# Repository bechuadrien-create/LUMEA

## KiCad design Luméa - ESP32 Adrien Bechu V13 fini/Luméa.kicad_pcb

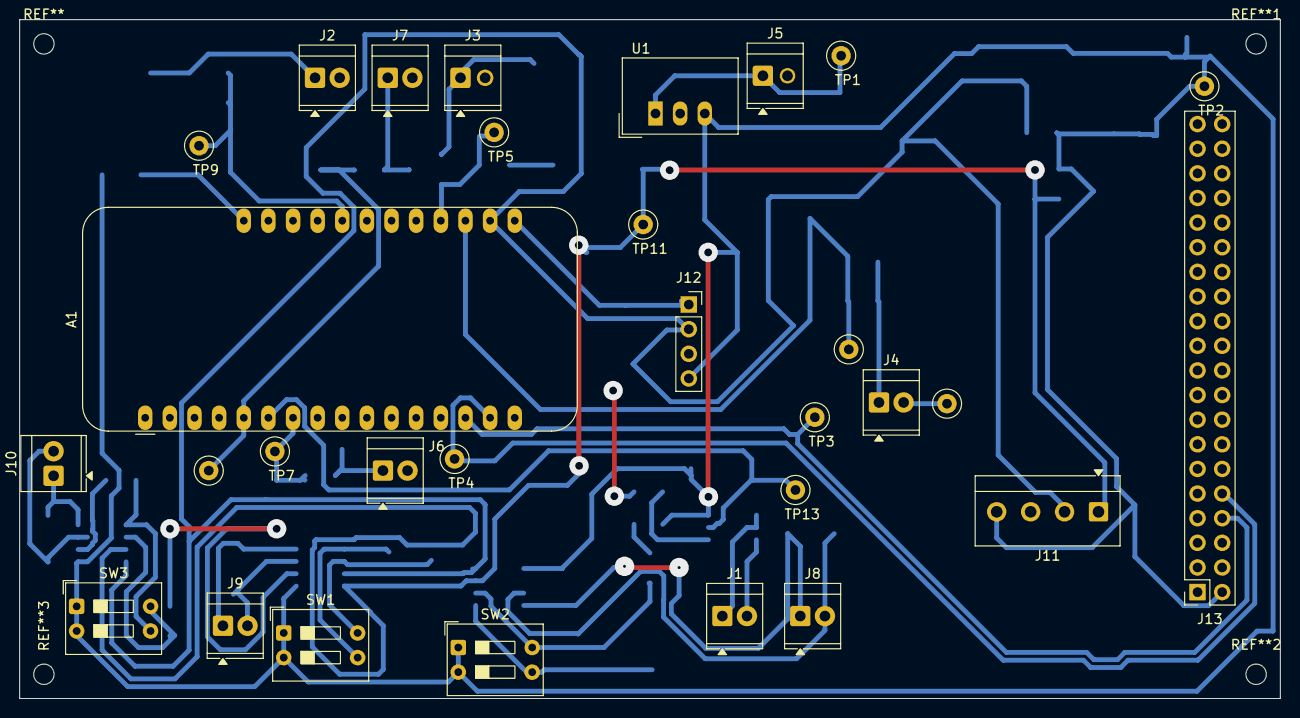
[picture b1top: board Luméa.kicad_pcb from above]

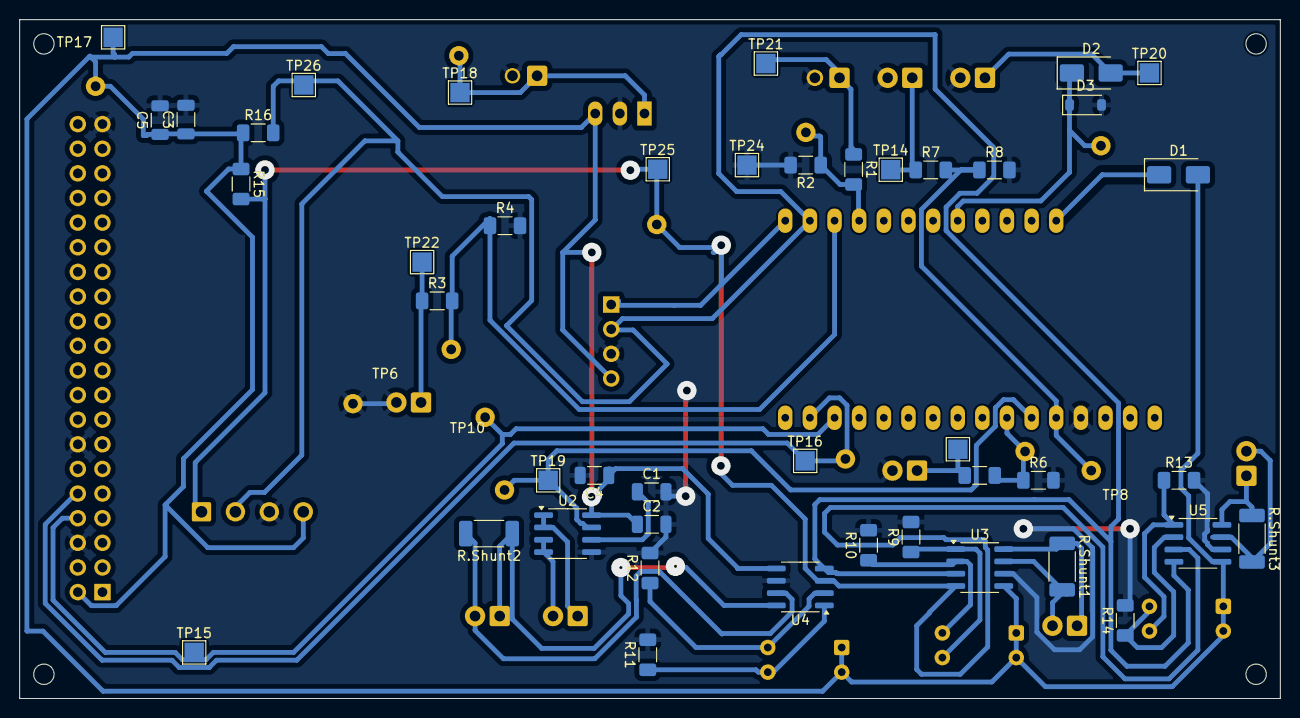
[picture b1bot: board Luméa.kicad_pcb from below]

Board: 2 copper layers, 130.0 x 70.0 mm, 74 parts (44 on the bottom side), 34 nets.

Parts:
A1: Adafruit_Feather_HUZZAH32_ESP32; Adafruit_Feather
C1: 100nF; C_1206_3216Metric
C2: 1nF; C_1206_3216Metric
C3, C4, C5: 1μF; C_1206_3216Metric
D1: B120-E3; D_SMA
D2: D; D_SMA
D3: D_Zener; D_SOD-123
J1, J3, J4, J5, J6, J7, J8, J9, J10: Screw_Terminal_01x02; TerminalBlock_TE_282834-2_1x02_P2.54mm_Horizontal
J2: Tension des panneaux photovoltaiques; TerminalBlock_TE_282834-2_1x02_P2.54mm_Horizontal
J11: BMP 280; TerminalBlock_4Ucon_1x04_P3.50mm_Horizontal
J12: TF051; PinSocket_1x04_P2.54mm_Vertical
J13: GPIO; PinSocket_2x20_P2.54mm_Vertical
R1, R3, R5, R7: 22K; R_1206_3216Metric_Pad1.30x1.75mm_HandSolder
R2, R4, R6, R8, R9, R10, R11, R12, R13, R14: 10K; R_1206_3216Metric_Pad1.30x1.75mm_HandSolder
R15: 4.7K; R_1206_3216Metric_Pad1.30x1.75mm_HandSolder
R16: 4.7k; R_1206_3216Metric_Pad1.30x1.75mm_HandSolder
R.Shunt1, R.Shunt2, R.Shunt3: 0.1; R_2010_5025Metric_Pad1.40x2.65mm_HandSolder
SW1, SW2, SW3: SW_DIP_x02; SW_DIP_SPSTx02_Slide_9.78x7.26mm_W7.62mm_P2.54mm
TP1: Test 12V; TestPoint_Loop_D2.50mm_Drill1.0mm_LowProfile
TP2: Test 5V; TestPoint_Loop_D2.50mm_Drill1.0mm_LowProfile
TP3: Test RX; TestPoint_Loop_D2.50mm_Drill1.0mm_LowProfile
TP4: Test TX; TestPoint_Loop_D2.50mm_Drill1.0mm_LowProfile
TP5, TP6, TP7, TP9, TP13: TestPoint; TestPoint_Loop_D2.50mm_Drill1.0mm_LowProfile
TP8: Batterie; TestPoint_Loop_D2.50mm_Drill1.0mm_LowProfile
TP10: Test GND; TestPoint_Loop_D2.50mm_Drill1.0mm_LowProfile
TP11: Test SDA; TestPoint_Loop_D2.50mm_Drill1.0mm_LowProfile
TP14, TP19, TP20, TP21, TP22, TP23: TestPoint_Alt; TestPoint_Pad_2.0x2.0mm
TP15: Test RX; TestPoint_Pad_2.0x2.0mm
TP16: Test TX; TestPoint_Pad_2.0x2.0mm
TP17: Test 5V; TestPoint_Pad_2.0x2.0mm
TP18: Test 12V; TestPoint_Pad_2.0x2.0mm
TP24: Test GND; TestPoint_Pad_2.0x2.0mm
TP25: Test SDA; TestPoint_Pad_2.0x2.0mm
TP26: Test SCL; TestPoint_Pad_2.0x2.0mm
U1: TSR_1-2450; Converter_DCDC_TRACO_TSR-1_THT
U2: ACS712xLCTR-20A; SOIC-8_3.9x4.9mm_P1.27mm
U3, U4, U5: INA219AxD; SOIC-8_3.9x4.9mm_P1.27mm

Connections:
+5V: C2.1, C3.1, C4.1, C5.1, D1.2 (A), J11.4, J12.4, J13.2, R15.1, R16.1, SW1.1, SW1.2, SW2.1, SW2.2, SW3.1, SW3.2, TP2.1, TP17.1, U1.3 (Vout), U2.8 (VCC), U3.5 (VS), U4.5 (VS), U5.5 (VS)
/ALIM/Test 12V: J5.1, TP1.1, TP18.1, U1.1 (Vin)
/Capteur analogique/A1: A1.6 (DAC1/A1), TP13.1, TP19.1, U2.7 (VIOUT)
/Capteur de Courant/SCL: A1.18 (SCL/IO22), J11.2, J12.2, R16.2, TP26.1, U3.3 (SDA), U4.4 (SCL), U5.4 (SCL)
/Capteur de Courant/SDA: A1.17 (SDA/IO23), J11.1, J12.1, R15.2, TP11.1, TP25.1, U3.4 (SCL), U4.3 (SDA), U5.3 (SDA)
/Micro-Controleur/+5V ESP32: A1.28 (VBAT), D1.1 (K)
/Micro-Controleur/RX: A1.14 (RX/IO16), J13.8, TP3.1, TP15.1
/Micro-Controleur/TX: A1.15 (TX/IO17), J13.10, TP4.1, TP16.1
/VBatt: A1.5 (DAC2/A0), R7.2, R8.1, TP8.1
/VEolienne: A1.24 (A11/IO12), D2.1 (K), D3.1 (K), TP9.1
/VLibre: A1.20 (A7/IO32), R1.2, R2.1, TP5.1
/VPS 1: A1.7 (I34/A2), R5.2, R6.1, TP7.1
/VPS 2: A1.19 (A6/IO14), R3.2, R4.1, TP6.1
GND: A1.4 (GND), C1.2, C2.2, C3.2, C4.2, C5.2, D3.2 (A), J2.2, J3.2, J4.2, J5.2, J6.2, J7.2, J11.3, J12.3, J13.6, J13.14, J13.39, R2.2, R4.2, R6.2, R8.2, R9.2, R10.2, R11.2, R12.2, R13.2, R14.2, TP10.1, TP24.1, U1.2 (GND), U2.5 (GND), U3.6 (GND), U4.6 (GND), U5.6 (GND)
unnamed: D2.2 (A), J2.1, TP20.1
unnamed: J1.1, U2.1 (IP+), U2.2 (IP+)
unnamed: J1.2, U2.3 (IP-), U2.4 (IP-)
unnamed: J3.1, R1.1, TP21.1
unnamed: J4.1, R3.1, TP22.1
unnamed: J6.1, R5.1, TP23.1
unnamed: J7.1, R7.1, TP14.1
unnamed: J8.1, R.Shunt2.1, U4.8 (IN+)
unnamed: J8.2, R.Shunt2.2, U4.7 (IN-)
unnamed: J9.1, R.Shunt1.1, U3.8 (IN+)
unnamed: J9.2, R.Shunt1.2, U3.7 (IN-)
unnamed: J10.1, R.Shunt3.1, U5.8 (IN+)
unnamed: J10.2, R.Shunt3.2, U5.7 (IN-)
unnamed: C1.1, U2.6 (FILTER)
unnamed: R10.1, SW1.4, U3.2 (A0)
unnamed: R9.1, SW1.3, U3.1 (A1)
unnamed: R12.1, SW2.4, U4.2 (A0)
unnamed: R11.1, SW2.3, U4.1 (A1)
unnamed: R14.1, SW3.4, U5.2 (A0)
unnamed: R13.1, SW3.3, U5.1 (A1)

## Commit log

2026-01-30 Premiére version du projet LUMEA
2026-01-30 LUMEA V2
2026-04-02 V13
    La version final
